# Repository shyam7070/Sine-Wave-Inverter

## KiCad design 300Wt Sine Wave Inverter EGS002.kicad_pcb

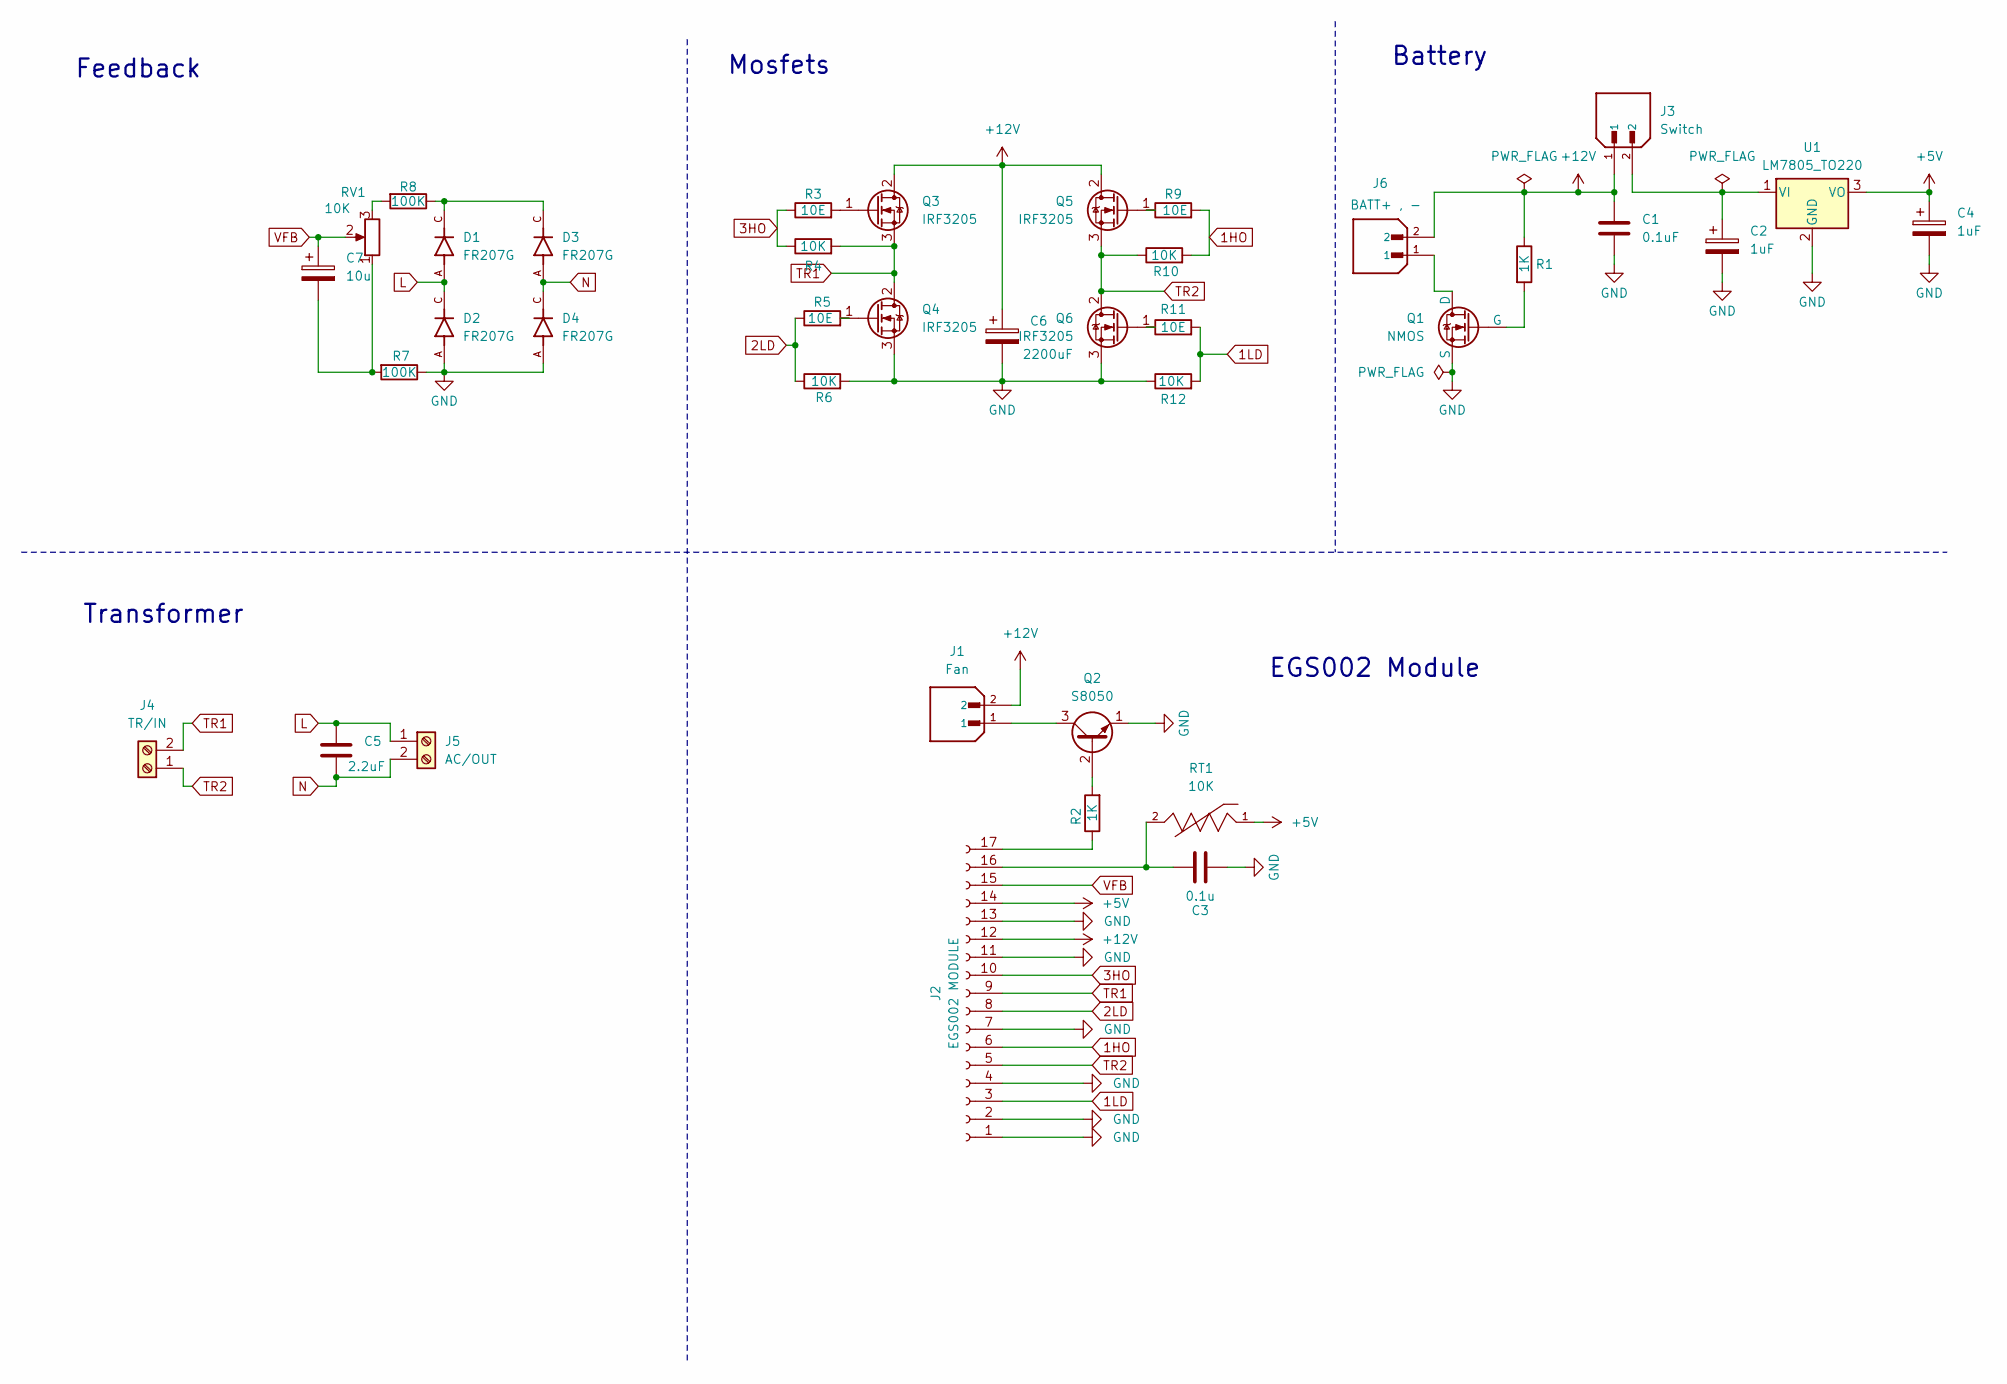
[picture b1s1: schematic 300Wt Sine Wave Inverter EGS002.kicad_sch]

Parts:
C1: 0.1uF; C_Disc_D4.3mm_W1.9mm_P5.00mm
C2, C4: 1uF; CP_Radial_D5.0mm_P2.50mm
C3: 0.1u; C_Disc_D4.3mm_W1.9mm_P5.00mm
C5: 2.2uF; C_Rect_L16.5mm_W6.0mm_P15.00mm_MKT
C6: 2200uF; CP_Radial_D12.5mm_P5.00mm
C7: 10u; CP_Radial_D5.0mm_P2.50mm
D1, D2, D3, D4: FR207G; DIOAD1300W80L670D310; PARTREV F2105
J1: Fan; JST_B2B-XH-A; PARTREV N/A
J2: EGS002 MODULE; PinSocket_1x17_P2.54mm_Vertical
J3: Switch; JST_B2B-XH-A; PARTREV N/A
J4: TR/IN; TerminalBlock_bornier-2_P5.08mm
J5: AC/OUT; TerminalBlock_bornier-2_P5.08mm
J6: BATT+ , -; JST_B2B-XH-A; PARTREV N/A
Q1: NMOS; TO-252-2
Q2: S8050; TO-92_Inline
Q3, Q4, Q5, Q6: IRF3205; TO-220-3_Vertical
R1, R2: 1K; R_Axial_DIN0207_L6.3mm_D2.5mm_P7.62mm_Horizontal
R3, R5, R9, R11: 10E; R_Axial_DIN0207_L6.3mm_D2.5mm_P7.62mm_Horizontal
R4, R6, R10, R12: 10K; R_Axial_DIN0207_L6.3mm_D2.5mm_P7.62mm_Horizontal
R7, R8: 100K; R_Axial_DIN0207_L6.3mm_D2.5mm_P7.62mm_Horizontal
RT1: 10K; THERM_NXRT15XH103FA5B030; PARTREV N/A
RV1: 10K; Potentiometer_Bourns_3296W_Vertical
U1: LM7805_TO220; TO-220-3_Vertical

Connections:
1HO: J2.6, R9.2, R10.2
1LD: J2.3, R11.2, R12.2
2LD: J2.8, R5.1, R6.1
3HO: J2.10, R3.1, R4.1
+5V: C4.1, J2.14, RT1.1, U1.3 (VO)
+12V: C1.1, C6.1, J1.2, J2.12, J3.1, J6.2, Q3.2 (D), Q5.2 (D), R1.1
GND: C1.2, C2.2, C3.2, C4.2, C6.2, D2.A, D4.A, J2.1, J2.2, J2.4, J2.7, J2.11, J2.13, Q1.3 (S), Q2.1 (E), Q4.3 (S), Q6.3 (S), R6.2, R7.1, R12.1, U1.2 (GND)
L: C5.1, D1.A, D2.C, J5.1
N: C5.2, D3.A, D4.C, J5.2
unnamed: C7.2, R7.2, RV1.1
unnamed: D1.C, D3.C, R8.1
unnamed: C3.1, J2.16, RT1.2
unnamed: J2.17, R2.1
unnamed: J6.1, Q1.1 (D)
unnamed: Q1.2 (G), R1.2
unnamed: Q2.2 (B), R2.2
unnamed: J1.1, Q2.3 (C)
unnamed: Q3.1 (G), R3.2
unnamed: Q4.1 (G), R5.2
unnamed: Q5.1 (G), R9.1
unnamed: Q6.1 (G), R11.1
unnamed: R8.2, RV1.3
unnamed: C2.1, J3.2, U1.1 (VI)
TR1: J2.9, J4.2, Q3.3 (S), Q4.2 (D), R4.2
TR2: J2.5, J4.1, Q5.3 (S), Q6.2 (D), R10.1
VFB: C7.1, J2.15, RV1.2

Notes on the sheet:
Feedback
EGS002 Module
Transformer
Mosfets
Battery

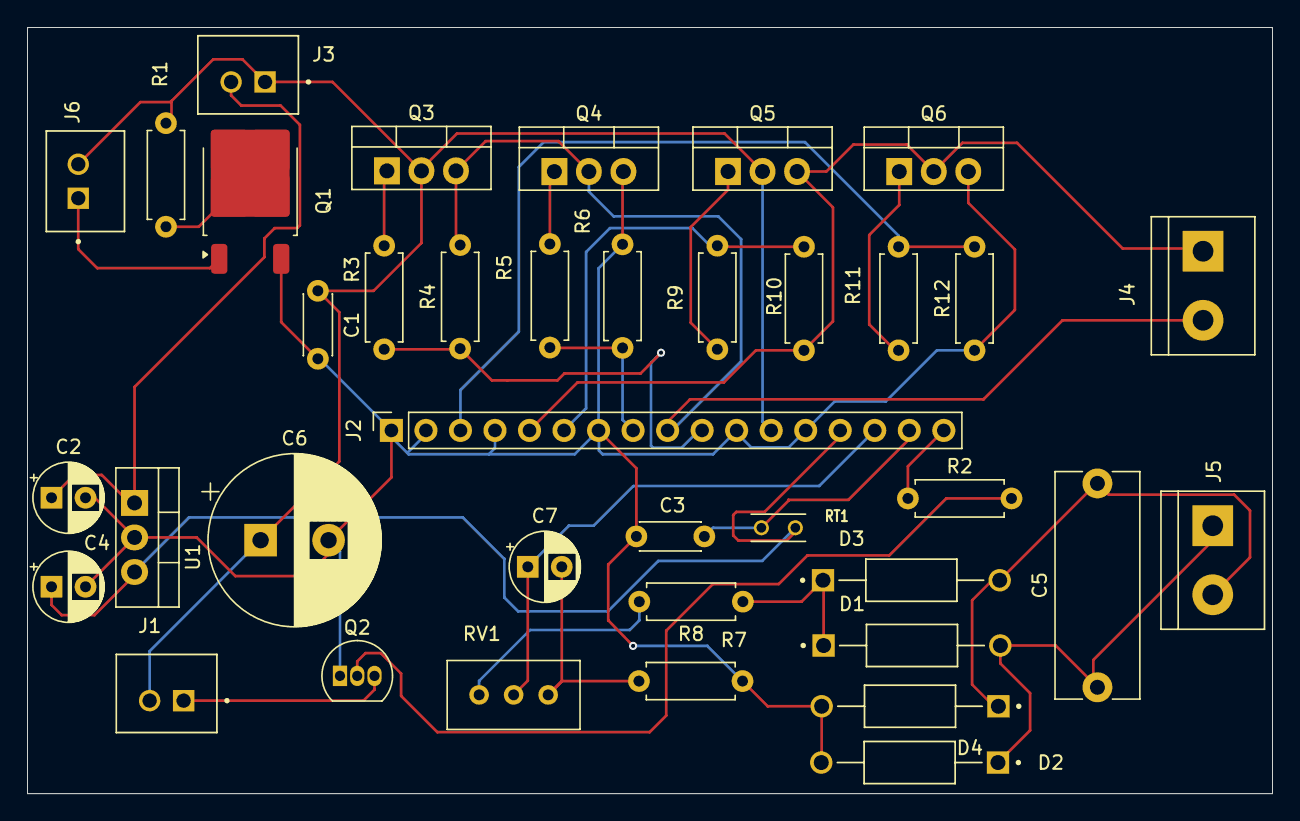
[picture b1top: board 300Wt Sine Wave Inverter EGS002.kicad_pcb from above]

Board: 2 copper layers, 91.6 x 56.4 mm, 38 parts (0 on the bottom side), 26 nets.
